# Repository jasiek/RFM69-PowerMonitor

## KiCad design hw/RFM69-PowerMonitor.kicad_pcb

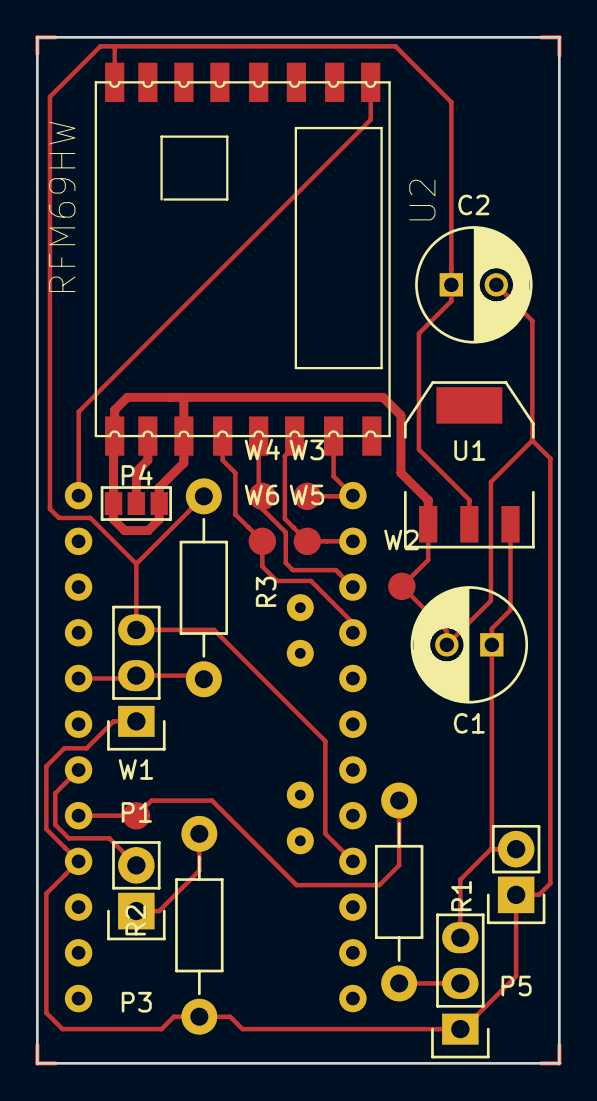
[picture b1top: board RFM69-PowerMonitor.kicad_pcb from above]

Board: 2 copper layers, 29.0 x 57.0 mm, 19 parts (1 on the bottom side), 14 nets.

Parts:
C1: 10uF; C_Radial_D6.3_L11.2_P2.5
C2: 100uF; C_Radial_D6.3_L11.2_P2.5
P1: CONN_1WIRE; Pin_Header_Straight_1x03
P2: CONN_PIR; Pin_Header_Straight_1x03
P3: CONN_METER; Pin_Header_Straight_1x02
P4: CONN_ANT; GS3
P5: CONN_PWR; Pin_Header_Straight_1x02
R1, R2: 470; Resistor_Horizontal_RM10mm
R3: 2.2k; Resistor_Horizontal_RM10mm
U1: AP1117D33; SOT-223
U2: RFM69HW; RFM
W1: TEST_PIR; Measurement_Point_Round-SMD-Pad_Small
W2: TEST_METER; Measurement_Point_Round-SMD-Pad_Small
W3: TEST_NSS; Measurement_Point_Round-SMD-Pad_Small
W4: TEST_MISO; Measurement_Point_Round-SMD-Pad_Small
W5: TEST_MOSI; Measurement_Point_Round-SMD-Pad_Small
W6: TEST_SCK; Measurement_Point_Round-SMD-Pad_Small
uP1: ARDUPROMINI-6; ArduProMini-6

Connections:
+5V: C1.1, P2.3, P5.2, U1.3
GND: C1.2, C2.2, P1.1, P2.1, P4.1, P4.3, P5.1, R2.1, U1.1, U2.GNDA, U2.GNDB, W2.1, uP1.10
unnamed: C2.1, P1.3, R3.1, U1.2, U2.VCC, uP1.22
unnamed: P1.2, R3.2, uP1.14
unnamed: P2.2, R1.2
unnamed: P3.1, R2.2
unnamed: P3.2, uP1.12
unnamed: P4.2, U2.ANT
unnamed: R1.1, W1.1, uP1.11
unnamed: U2.MISO, W4.1, uP1.28
unnamed: U2.MOSI, W5.1, uP1.29
unnamed: U2.NSS, W3.1, uP1.30
unnamed: U2.RESE, uP1.18
unnamed: U2.SCK, W6.1, uP1.27

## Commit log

2016-06-13 Initial commit with imported schema+footprint for RFM69HW from snapeda.
2016-06-13 Added component+footprint for the arduino mini pro.
2016-06-14 Generated netlist, assigned footprints.
2016-06-14 PCB done.
2016-06-14 Final PCB design.
2016-06-14 Added a panel of 5 boards.
2016-06-14 Generated production outputs for UV production.
2016-06-20 Removed a few PCB annotations to clean it up.
2016-06-20 Generated a skeletal project for the node.
2016-06-20 Initial implementation of the node.
